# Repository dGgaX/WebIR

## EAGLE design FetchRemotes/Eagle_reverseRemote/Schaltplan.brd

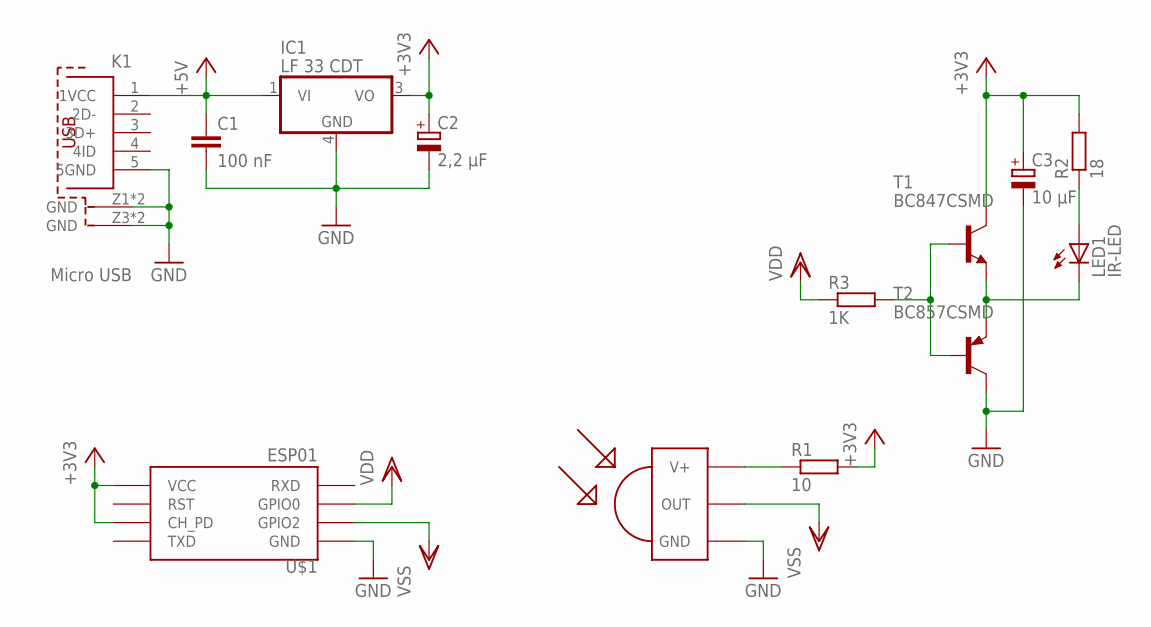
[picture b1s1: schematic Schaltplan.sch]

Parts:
C1: 100 nF; C0805K
C2: 2,2 µF; E2,5-5
C3: 10 µF; E2,5-5
IC1: LF 33 CDT; DPACK_3
IR-TRANSMITTER: TSOP1833; TSOP18XX
K1: Micro USB; 629105150521
LED1: IR-LED; LED5MM
R1: 10; M0805
R2: 18; M0805
R3: 1K; M0805
T1: BC847CSMD; SOT23
T2: BC857CSMD; SOT23-BEC
U$1: ESP01

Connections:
+3V3: C2.+, C3.+, IC1.3 (VO), R1.2, R2.2, T1.3 (C), U$1.CH_PD, U$1.VCC
+5V: C1.1, IC1.1 (VI), K1.1 (1VCC)
GND: C1.2, C2.-, C3.-, IC1.4 (GND), IR-TRANSMITTER.GND, K1.5 (5GND), K1.Z1 (GND), K1.Z2 (GND), K1.Z3 (GND), K1.Z4 (GND), T2.C, U$1.GND
unnamed: IR-TRANSMITTER.VCC (V+), R1.1
unnamed: R3.2, T1.1 (B), T2.B
unnamed: LED1.K (C), T1.2 (E), T2.E
unnamed: LED1.A, R2.1
VDD: R3.1, U$1.GPIO0
VSS: IR-TRANSMITTER.OUT, U$1.GPIO2

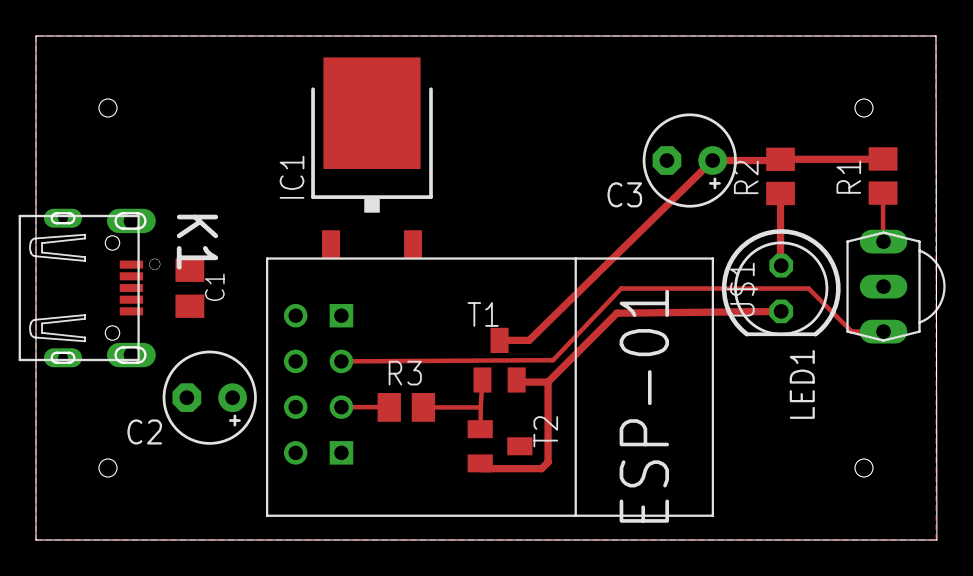
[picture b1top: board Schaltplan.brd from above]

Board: 2 copper layers, 49.9 x 27.9 mm, 13 parts (0 on the bottom side), 9 nets.

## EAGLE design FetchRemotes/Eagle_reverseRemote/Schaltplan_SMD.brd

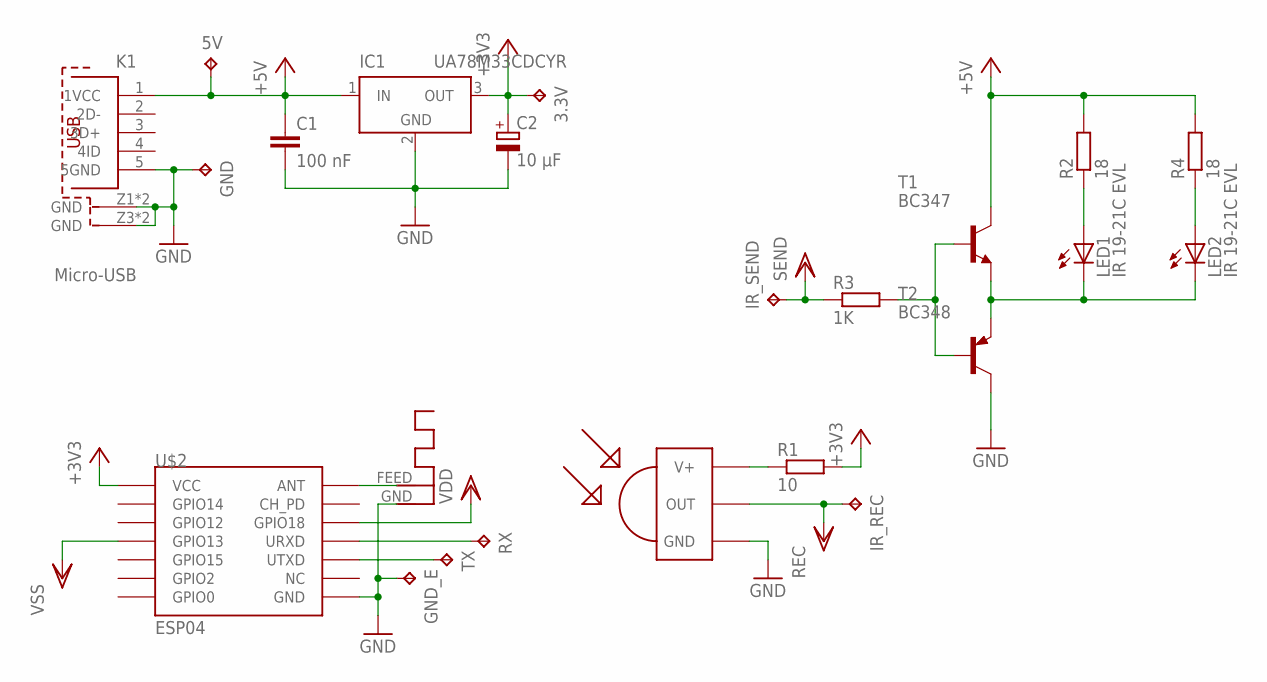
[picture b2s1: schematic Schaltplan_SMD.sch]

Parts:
3.3V, 5V: TPB2,54; B2,54
ANT1: ANTENNA; RN-ANT
C1: 100 nF; C0504
C2: 10 µF; UD-4X5,8_NICHICON
GND: TPB2,54; B2,54
GND_E: TPB2,54; B2,54
IC1: UA78M33CDCYR; SOT223
IR-TRANSMITTER: TSOP1833; TSOP18XX
IR_REC: TPB2,54; B2,54
IR_SEND: TPB2,54; B2,54
K1: Micro-USB; 629105150521
LED1, LED2: IR 19-21C EVL; CHIPLED_1206
R1: 10; R1206W
R2, R4: 18; R1206W
R3: 1K; R1206W
RX: TPB2,54; B2,54
T1: BC347; SOT23-EBC
T2: BC348; SOT23-BCE
TX: TPB2,54; B2,54
U$2: ESP04

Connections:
+3V3: 3.3V.TP, C2.+, IC1.3 (OUT), R1.2, U$2.VCC
+5V: 5V.TP, C1.1, IC1.1 (IN), K1.1 (1VCC), R2.2, R4.2, T1.C
GND: ANT1.GND, C1.2, C2.-, GND.TP, GND_E.TP, IC1.2 (GND), IC1.4 (GND), IR-TRANSMITTER.GND, K1.5 (5GND), K1.Z1 (GND), K1.Z2 (GND), K1.Z3 (GND), K1.Z4 (GND), T2.C, U$2.GND
unnamed: IR-TRANSMITTER.VCC (V+), R1.1
unnamed: R3.2, T1.B, T2.B
unnamed: ANT1.FEED, U$2.ANT
unnamed: RX.TP, U$2.URXD
unnamed: TX.TP, U$2.UTXD
unnamed: LED2.A, R4.1
unnamed: LED1.C, LED2.C, T1.E, T2.E
unnamed: LED1.A, R2.1
SEND: IR_SEND.TP, R3.1, U$2.GPIO18
VSS: IR-TRANSMITTER.OUT, IR_REC.TP, U$2.GPIO13

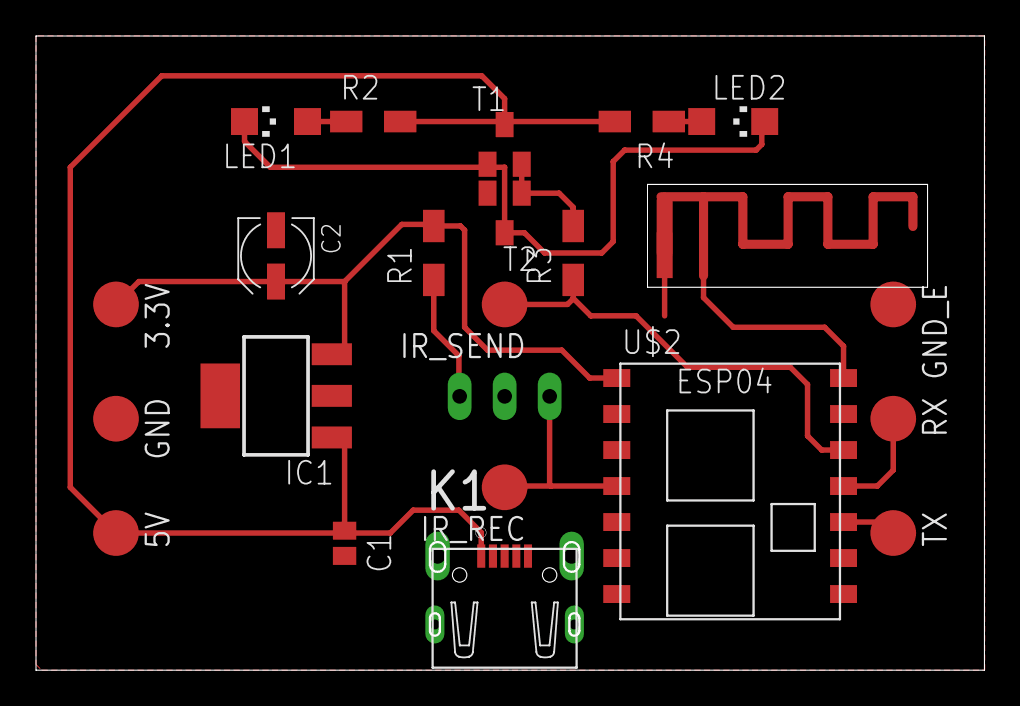
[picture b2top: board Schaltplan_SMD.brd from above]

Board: 2 copper layers, 52.6 x 35.1 mm, 23 parts (1 on the bottom side), 13 nets.

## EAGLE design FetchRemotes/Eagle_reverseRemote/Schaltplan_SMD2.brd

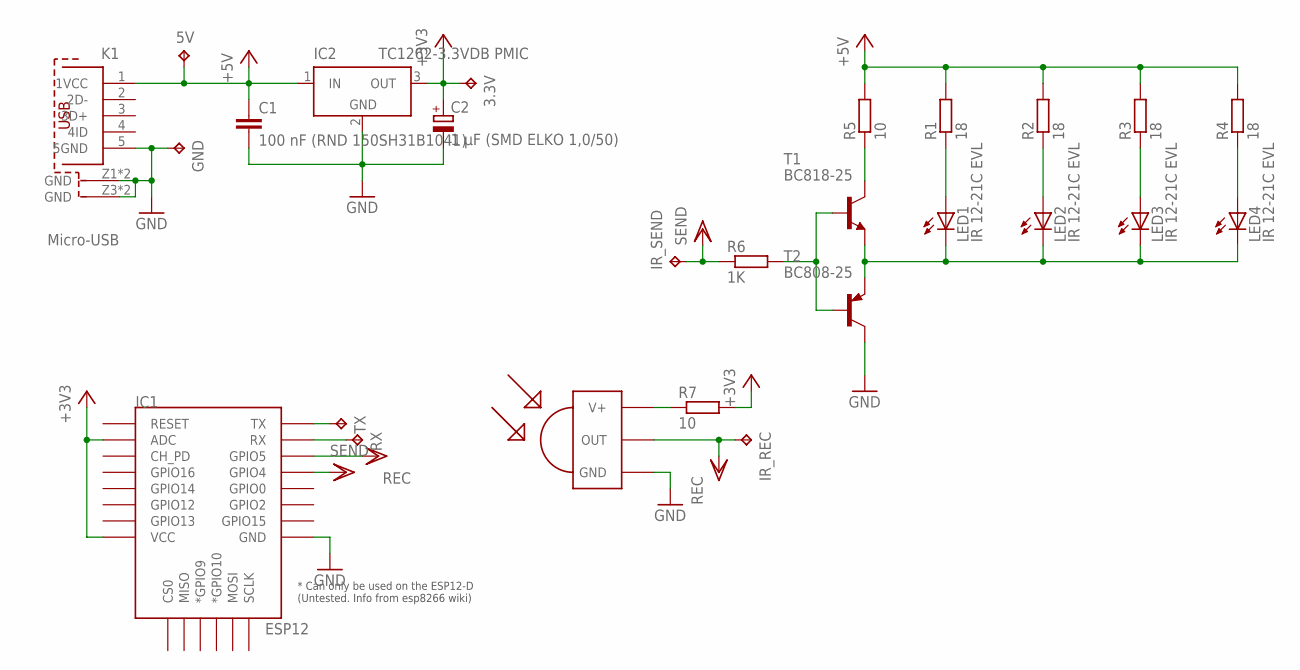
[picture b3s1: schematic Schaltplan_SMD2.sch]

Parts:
3.3V, 5V: TPB2,54; B2,54
C1: 100 nF (RND 150SH31B1041); C1206
C2: 1 µF (SMD ELKO 1,0/50); UD-4X5,8_NICHICON
GND: TPB2,54; B2,54
IC1: ESP12; ESP12E-SMD
IC2: TC1262-3.3VDB PMIC; SOT223
IR-TRANSMITTER: TSOP1833; TSOP18XX
IR_REC: TPB2,54; B2,54
IR_SEND: TPB2,54; B2,54
K1: Micro-USB; 629105150521
LED1, LED2, LED3, LED4: IR 12-21C EVL; CHIPLED_1206
R1, R2, R3, R4: 18; R1206W
R5, R7: 10; R1206W
R6: 1K; R1206W
RX: TPB2,54; B2,54
T1: BC818-25; SOT23-BEC
T2: BC808-25; SOT23-BEC
TX: TPB2,54; B2,54

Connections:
+3V3: 3.3V.TP, C2.+, IC1.ADC, IC1.VCC, IC2.3 (OUT), R7.2
+3V3T: IR-TRANSMITTER.VCC (V+), R7.1
+5V: 5V.TP, C1.1, IC2.1 (IN), K1.1 (1VCC), R1.2, R2.2, R3.2, R4.2, R5.2
+5VT1: LED1.A, R1.1
+5VT2: LED2.A, R2.1
+5VT3: LED3.A, R3.1
+5VT4: LED4.A, R4.1
+5VT5: R5.1, T1.C
GND: C1.2, C2.-, GND.TP, IC1.GND, IC2.2 (GND), IC2.4 (GND), IR-TRANSMITTER.GND, K1.5 (5GND), K1.Z1 (GND), K1.Z2 (GND), K1.Z3 (GND), K1.Z4 (GND), T2.C
IR_REC: IC1.GPIO5, IR-TRANSMITTER.OUT, IR_REC.TP
IR_SEND: IC1.GPIO4, IR_SEND.TP, R6.1
unnamed: R6.2, T1.B, T2.B
RX: IC1.RXD0 (RX), RX.TP
SWITCHED: LED1.C, LED2.C, LED3.C, LED4.C, T1.E, T2.E
TX: IC1.TXD0 (TX), TX.TP

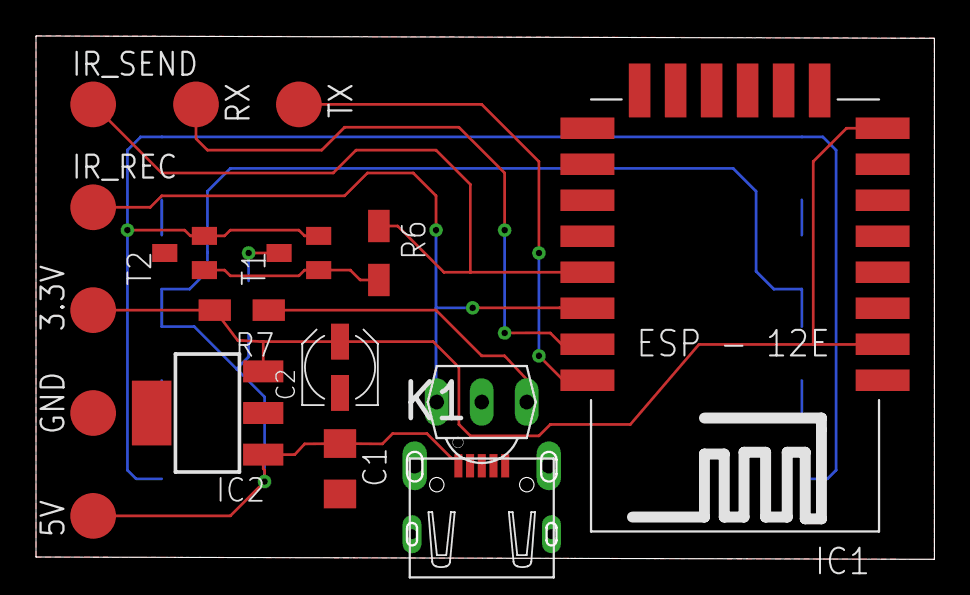
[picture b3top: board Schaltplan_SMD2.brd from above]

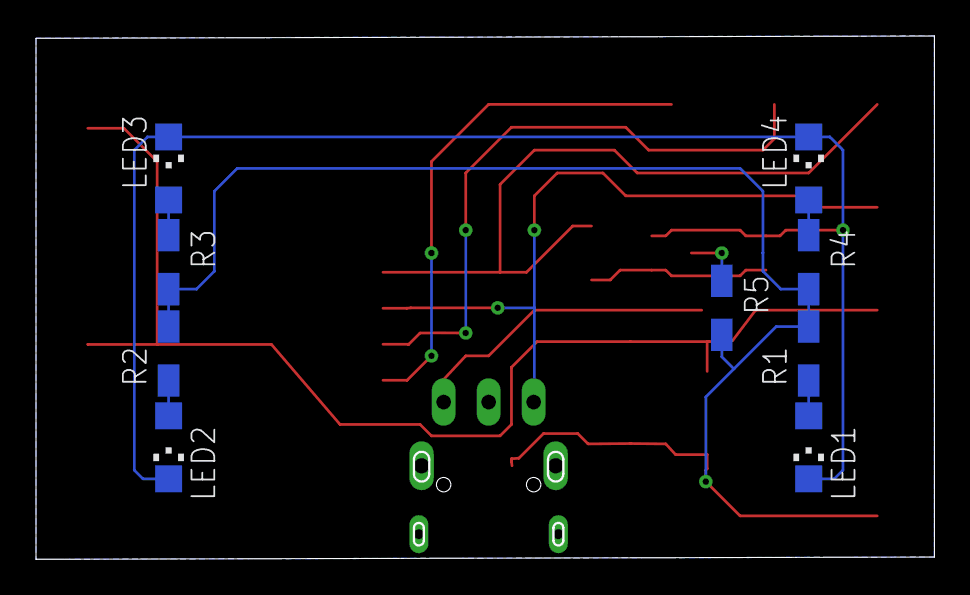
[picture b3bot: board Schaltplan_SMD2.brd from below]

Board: 2 copper layers, 49.8 x 28.9 mm, 26 parts (9 on the bottom side), 15 nets.

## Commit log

2018-07-09 Erste fast lauffähige Version ...
    Datei öffnen fehlt noch
2018-07-10 Abfertigung des Wizards geändert.
2018-07-11 23bit & x64 - Versionen
2018-07-11 Open File gemacht!
2018-07-12 incoming & outgoing gesetzt
2018-07-12 Minor Changes
2018-11-29 eagle hinzugefügt

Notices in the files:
parts and their libraries:
Wurth_Elektronik_Electromechanic_Input-O: Copyright: Würth Elektronik
